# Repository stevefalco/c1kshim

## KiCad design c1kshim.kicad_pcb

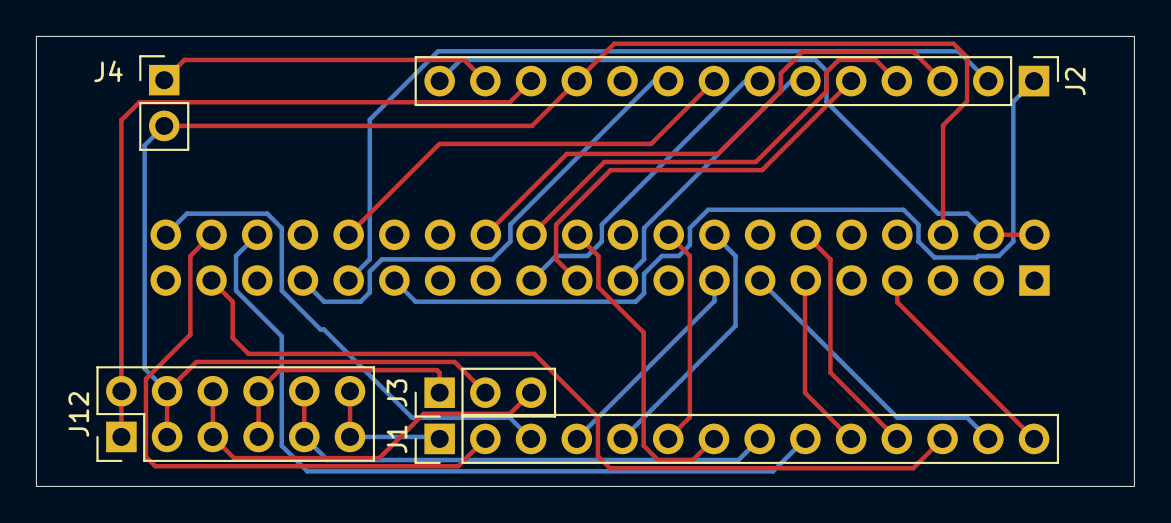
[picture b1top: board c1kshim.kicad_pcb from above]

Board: 2 copper layers, 61.0 x 25.0 mm, 6 parts (1 on the bottom side), 29 nets.

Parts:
J1, J2: Conn_01x14; PinHeader_1x14_P2.54mm_Vertical
J3: Conn_01x03; PinHeader_1x03_P2.54mm_Vertical
J4: Conn_01x02; PinHeader_1x02_P2.54mm_Vertical
J11: Conn_02x20_Odd_Even; PinHeader_2x20_P2.54mm_Vertical
J12: Conn_02x06_Odd_Even; PinHeader_2x06_P2.54mm_Vertical

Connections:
/COL0: J1.12, J11.37
/COL1: J1.13, J11.13
/COL2: J1.14, J11.7
/COL3: J2.1, J11.29
/COL4: J2.2, J11.31
/COL5: J2.3, J11.26
/COL6: J2.4, J11.24
/COL7: J2.5, J11.21
/COL8: J2.6, J11.19
/COL9: J2.7, J11.23
/COL10: J2.8, J11.32
/COL11: J2.9, J11.33
/GND: J2.11, J3.2, J4.2, J11.6, J12.3, J12.4
/GPIO0: J1.1, J12.11, J12.12
/GPIO8: J1.8, J12.9, J12.10
/GPIO23: J3.1, J12.7, J12.8
/GPIO24: J3.3, J12.5, J12.6
/ROW0: J1.9, J11.36
/ROW1: J1.10, J11.11
/ROW2: J1.11, J11.12
/VCC5: J2.14, J11.2, J11.4
/VCC33: J2.12, J12.1, J12.2
/VIN: J2.13, J4.1
/XLED0: J1.2, J11.38
/XLED1: J1.3, J11.40
/XLED2: J1.4, J11.15
/XLED3: J1.5, J11.16
/XLED4: J1.6, J11.18
/XLED5: J1.7, J11.22

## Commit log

2021-02-03 Initial
2021-02-03 Correct comments
2021-02-04 Add silk comment
2021-11-24 Move to KiCad 6
